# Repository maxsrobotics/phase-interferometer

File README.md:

# phase-interferometer
A 2(or more)-element phase interferometric direction finder for 433 MHz using a passive phased array

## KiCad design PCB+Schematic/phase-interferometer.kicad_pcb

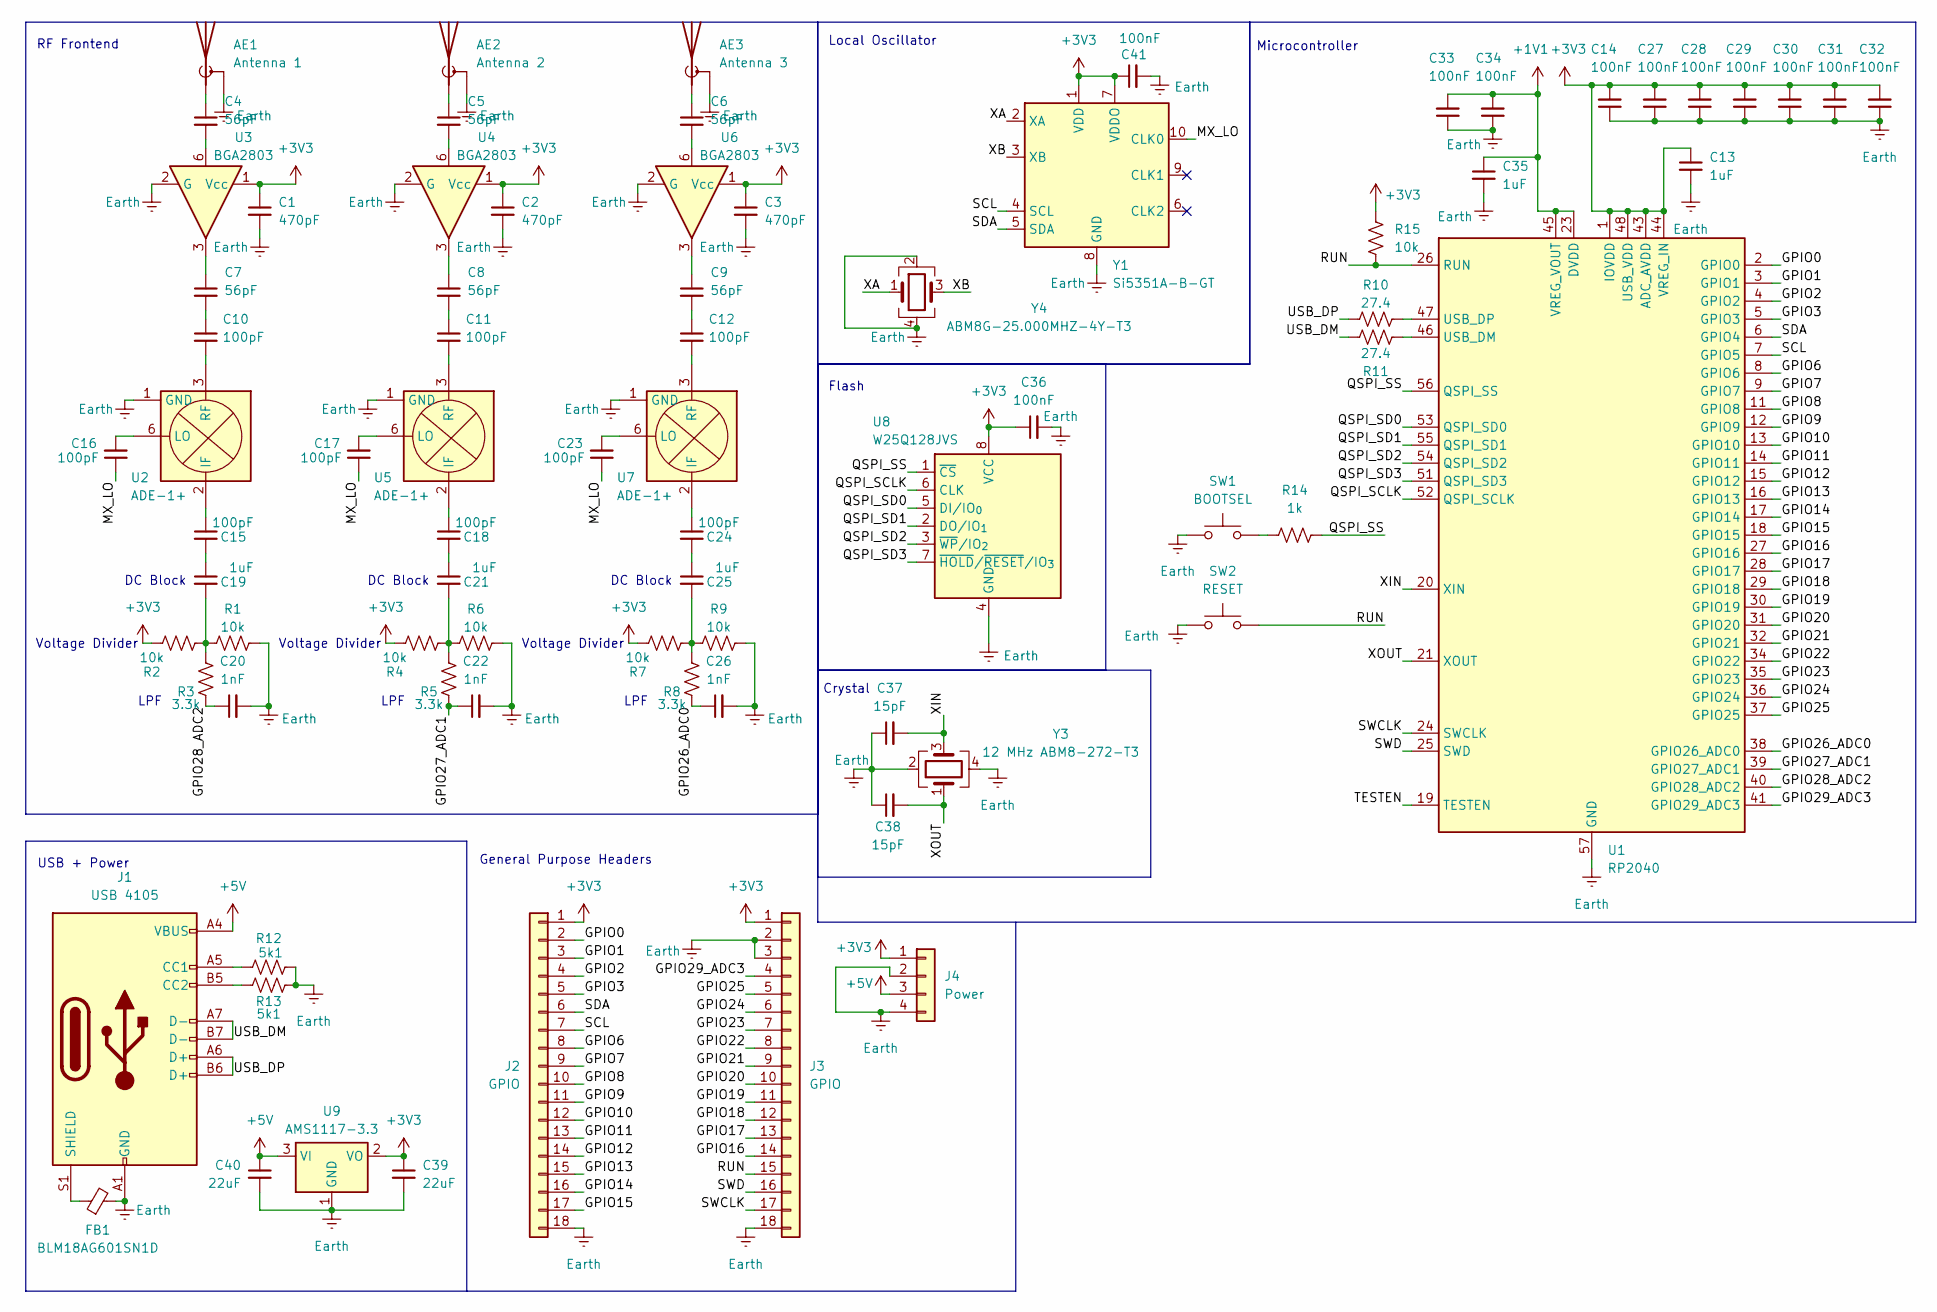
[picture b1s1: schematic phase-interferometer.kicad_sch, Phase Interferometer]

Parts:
AE1: Antenna 1; PinSocket_1x02_P2.54mm_Vertical
AE2: Antenna 2; PinSocket_1x02_P2.54mm_Vertical
AE3: Antenna 3; PinSocket_1x02_P2.54mm_Vertical
C1, C2, C3: 470pF; C_0603_1608Metric
C4, C5, C6, C7, C8, C9: 56pF; C_0603_1608Metric
C10, C11, C12, C15, C16, C17, C18, C23, C24: 100pF; C_0603_1608Metric
C13, C19, C21, C25, C35: 1uF; C_0603_1608Metric
C14, C27, C28, C29, C30, C31, C32, C33, C34, C36, C41: 100nF; C_0603_1608Metric
C20, C22, C26: 1nF; C_0603_1608Metric
C37, C38: 15pF; C_0603_1608Metric
C39, C40: 22uF; C_0603_1608Metric
FB1: BLM18AG601SN1D; R_0201_0603Metric
J1: USB 4105; USB_C_Receptacle_GCT_USB4105-xx-A_16P_TopMnt_Horizontal
J2, J3: GPIO; PinSocket_1x18_P2.54mm_Vertical
J4: Power; PinSocket_1x04_P2.54mm_Vertical
R1, R2, R4, R6, R7, R9, R15: 10k; R_0603_1608Metric
R3, R5, R8: 3.3k; R_0603_1608Metric
R10, R11: 27.4; R_0603_1608Metric
R12, R13: 5k1; R_0603_1608Metric
R14: 1k; R_0603_1608Metric
SW1: BOOTSEL; SW_Tactile_SPST_NO_Straight_CK_PTS636Sx25SMTRLFS
SW2: RESET; SW_Tactile_SPST_NO_Straight_CK_PTS636Sx25SMTRLFS
U1: RP2040; QFN-56-1EP_7x7mm_P0.4mm_EP3.2x3.2mm
U2, U5, U7: ADE-1+; Mini-Circuits_CD636_H4.11mm
U3, U4, U6: BGA2803; SOT-363_SC-70-6
U8: W25Q128JVS; SOIC-8_5.3x5.3mm_P1.27mm
U9: AMS1117-3.3; SOT-223-3_TabPin2
Y1: Si5351A-B-GT; MSOP-10_3x3mm_P0.5mm
Y3: 12 MHz ABM8-272-T3; Crystal_SMD_Abracon_ABM8G-4Pin_3.2x2.5mm
Y4: ABM8G-25.000MHZ-4Y-T3; Crystal_SMD_Abracon_ABM8G-4Pin_3.2x2.5mm

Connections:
+1V1: C33.2, C34.2, C35.1, U1.23 (DVDD), U1.45 (VREG_VOUT), U1.50 (DVDD)
+3V3: C1.1, C2.1, C3.1, C13.1, C14.2, C27.2, C28.2, C29.2, C30.2, C31.2, C32.2, C36.1, C39.1, C41.1, J2.1, J3.1, J4.1, R2.2, R4.2, R7.2, R15.1, U1.1 (IOVDD), U1.10 (IOVDD), U1.22 (IOVDD), U1.33 (IOVDD), U1.42 (IOVDD), U1.43 (ADC_AVDD), U1.44 (VREG_IN), U1.48 (USB_VDD), U1.49 (IOVDD), U3.1 (Vcc), U4.1 (Vcc), U6.1 (Vcc), U8.8 (VCC), U9.2 (VO), Y1.1 (VDD), Y1.7 (VDDO)
+5V: C40.1, J1.A4 (VBUS), J1.A9 (VBUS), J1.B4 (VBUS), J1.B9 (VBUS), J4.3, U9.3 (VI)
/GPIO0: J2.2, U1.2 (GPIO0)
/GPIO1: J2.3, U1.3 (GPIO1)
/GPIO2: J2.4, U1.4 (GPIO2)
/GPIO3: J2.5, U1.5 (GPIO3)
/GPIO6: J2.8, U1.8 (GPIO6)
/GPIO7: J2.9, U1.9 (GPIO7)
/GPIO8: J2.10, U1.11 (GPIO8)
/GPIO9: J2.11, U1.12 (GPIO9)
/GPIO10: J2.12, U1.13 (GPIO10)
/GPIO11: J2.13, U1.14 (GPIO11)
/GPIO12: J2.14, U1.15 (GPIO12)
/GPIO13: J2.15, U1.16 (GPIO13)
/GPIO14: J2.16, U1.17 (GPIO14)
/GPIO15: J2.17, U1.18 (GPIO15)
/GPIO16: J3.14, U1.27 (GPIO16)
/GPIO17: J3.13, U1.28 (GPIO17)
/GPIO18: J3.12, U1.29 (GPIO18)
/GPIO19: J3.11, U1.30 (GPIO19)
/GPIO20: J3.10, U1.31 (GPIO20)
/GPIO21: J3.9, U1.32 (GPIO21)
/GPIO22: J3.8, U1.34 (GPIO22)
/GPIO23: J3.7, U1.35 (GPIO23)
/GPIO24: J3.6, U1.36 (GPIO24)
/GPIO25: J3.5, U1.37 (GPIO25)
/GPIO26_ADC0: C26.1, R8.1, U1.38 (GPIO26_ADC0)
/GPIO27_ADC1: C22.1, R5.1, U1.39 (GPIO27_ADC1)
/GPIO28_ADC2: C20.1, R3.1, U1.40 (GPIO28_ADC2)
/GPIO29_ADC3: J3.4, U1.41 (GPIO29_ADC3)
/MX_LO: C16.1, C17.1, C23.1, Y1.10 (CLK0)
/QSPI_SCLK: U1.52 (QSPI_SCLK), U8.6 (CLK)
/QSPI_SD0: U1.53 (QSPI_SD0), U8.5 (DI/IO_{0})
/QSPI_SD1: U1.55 (QSPI_SD1), U8.2 (DO/IO_{1})
/QSPI_SD2: U1.54 (QSPI_SD2), U8.3 (~WP/IO_{2})
/QSPI_SD3: U1.51 (QSPI_SD3), U8.7 (~HOLD/~RESET/IO_{3})
/QSPI_SS: R14.2, U1.56 (QSPI_SS), U8.1 (~CS)
/RUN: J3.15, R15.2, SW2.2, U1.26 (RUN)
/SCL: J2.7, U1.7 (GPIO5), Y1.4 (SCL)
/SDA: J2.6, U1.6 (GPIO4), Y1.5 (SDA)
/SWCLK: J3.17, U1.24 (SWCLK)
/SWD: J3.16, U1.25 (SWD)
/TESTEN: U1.19 (TESTEN)
/USB_DM: J1.A7 (D-), J1.B7 (D-), R11.2
/USB_DP: J1.A6 (D+), J1.B6 (D+), R10.1
/XA: Y1.2 (XA), Y4.1
/XB: Y1.3 (XB), Y4.3
/XIN: C37.2, U1.20 (XIN), Y3.3
/XOUT: C38.2, U1.21 (XOUT), Y3.1
Earth: AE1.2 (Shield), AE2.2 (Shield), AE3.2 (Shield), C1.2, C2.2, C3.2, C13.2, C14.1, C20.2, C22.2, C26.2, C27.1, C28.1, C29.1, C30.1, C31.1, C32.1, C33.1, C34.1, C35.2, C36.2, C37.1, C38.1, C39.2, C40.2, C41.2, FB1.2, J1.A1 (GND), J1.A12 (GND), J1.B1 (GND), J1.B12 (GND), J2.18, J3.2, J3.3, J3.18, J4.2, J4.4, R1.2, R6.2, R9.2, R12.2, R13.2, SW1.1, SW2.1, U1.57 (GND), U2.1 (GND), U2.4 (GND), U2.5 (GND), U3.2 (G), U3.4 (G), U3.5 (G), U4.2 (G), U4.4 (G), U4.5 (G), U5.1 (GND), U5.4 (GND), U5.5 (GND), U6.2 (G), U6.4 (G), U6.5 (G), U7.1 (GND), U7.4 (GND), U7.5 (GND), U8.4 (GND), U9.1 (GND), Y1.8 (GND), Y3.2, Y3.4, Y4.2, Y4.4
unnamed: AE1.1 (A), C4.1
unnamed: AE2.1 (A), C5.1
unnamed: AE3.1 (A), C6.1
unnamed: C4.2, U3.6
unnamed: C5.2, U4.6
unnamed: C6.2, U6.6
unnamed: C7.1, U3.3
unnamed: C8.1, U4.3
unnamed: C9.1, U6.3
unnamed: C7.2, C10.1
unnamed: C8.2, C11.1
unnamed: C9.2, C12.1
unnamed: C15.2, C19.1
unnamed: C18.2, C21.1
unnamed: C19.2, R1.1, R2.1, R3.2
unnamed: C21.2, R4.1, R5.2, R6.1
unnamed: C24.2, C25.1
unnamed: C25.2, R7.1, R8.2, R9.1
unnamed: J1.A5 (CC1), R12.1
unnamed: J1.B5 (CC2), R13.1
unnamed: FB1.1, J1.S1 (SHIELD)
unnamed: R14.1, SW1.2
unnamed: R11.1, U1.46 (USB_DM)
unnamed: R10.2, U1.47 (USB_DP)
unnamed: C15.1, U2.2 (IF)
unnamed: C16.2, U2.6 (LO)
unnamed: C10.2, U2.3 (RF)
unnamed: C18.1, U5.2 (IF)
unnamed: C17.2, U5.6 (LO)
unnamed: C11.2, U5.3 (RF)
unnamed: C24.1, U7.2 (IF)
unnamed: C23.2, U7.6 (LO)
unnamed: C12.2, U7.3 (RF)

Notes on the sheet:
LPF
Local Oscillator
Voltage Divider
DC Block
USB + Power
General Purpose Headers
Microcontroller
Flash
Crystal
RF Frontend

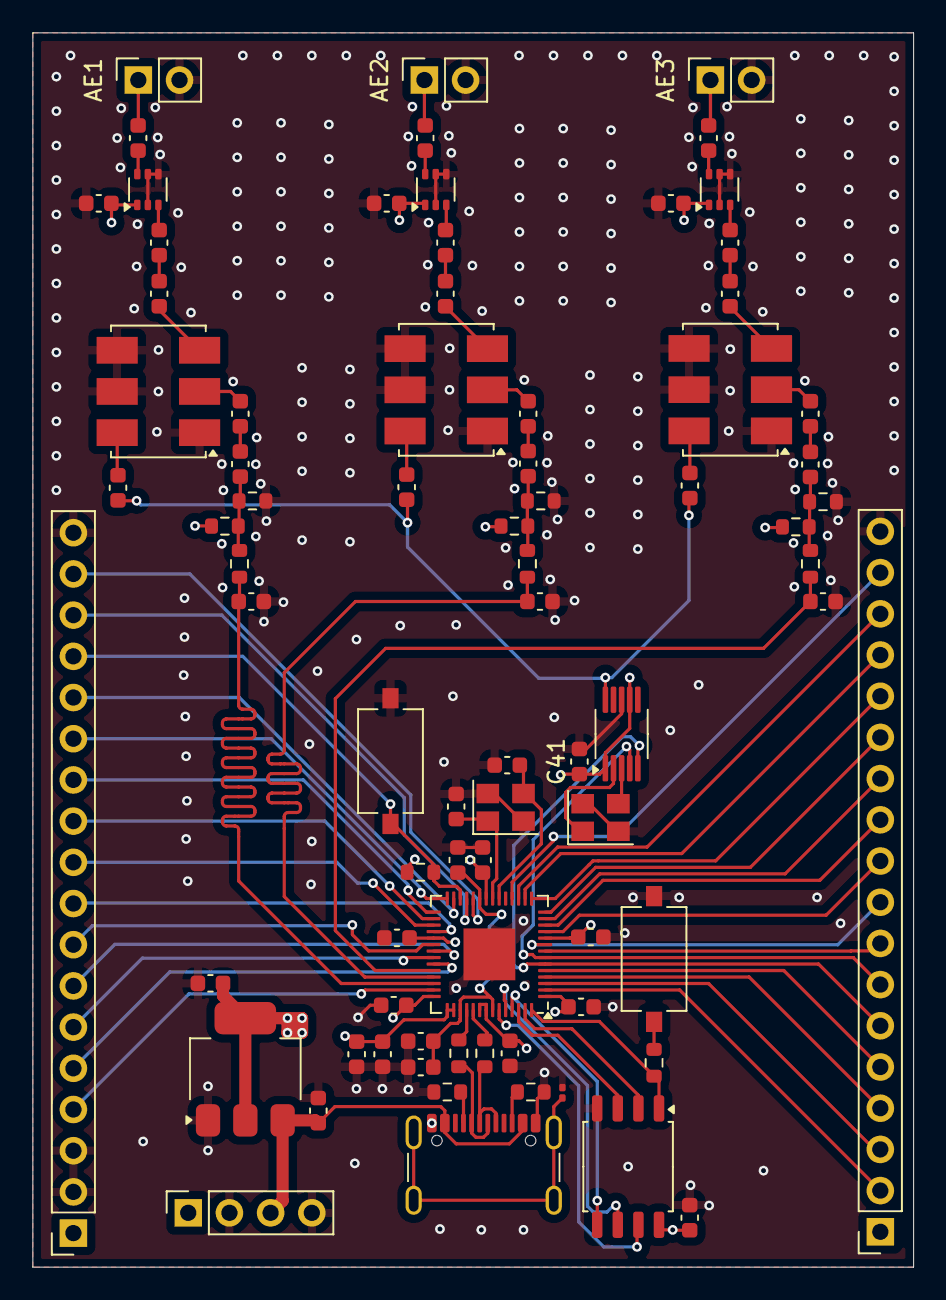
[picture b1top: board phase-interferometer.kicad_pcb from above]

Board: 4 copper layers, 54.3 x 76.1 mm, 78 parts (0 on the bottom side), 83 nets.

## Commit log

2025-04-22 file structure
2025-04-24 RF Frontend, MCU
2025-05-17 finish pcb!
2025-05-17 production files
2025-05-17 dru file
